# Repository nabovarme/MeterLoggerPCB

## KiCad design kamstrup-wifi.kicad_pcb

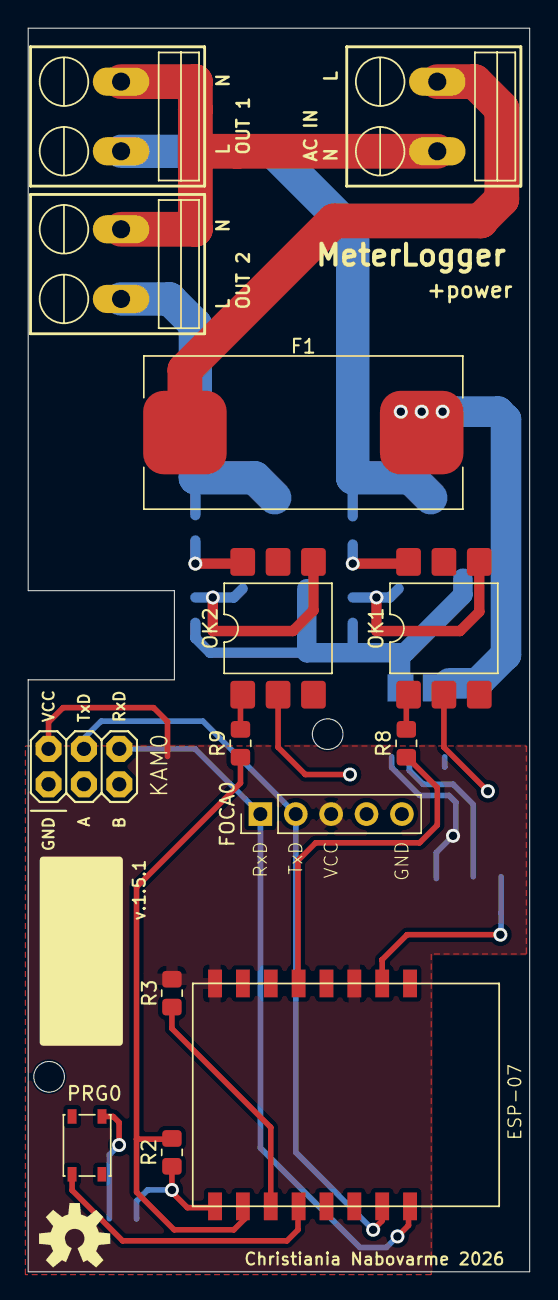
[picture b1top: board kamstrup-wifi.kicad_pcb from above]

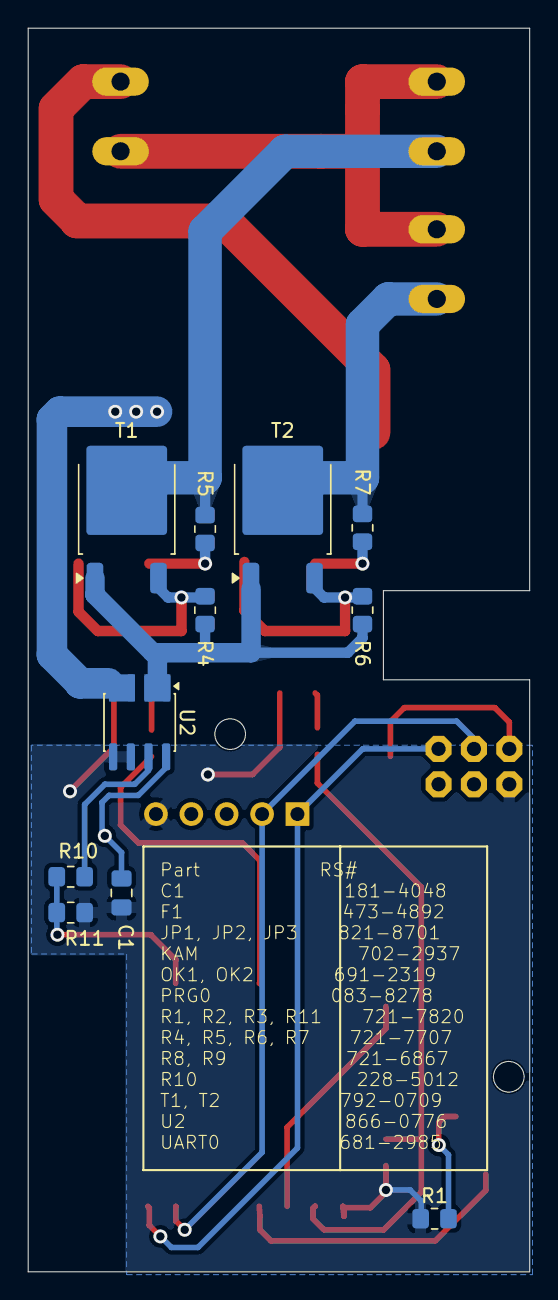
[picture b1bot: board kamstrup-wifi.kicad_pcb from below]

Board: 2 copper layers, 36.0 x 89.3 mm, 28 parts (11 on the bottom side), 23 nets.

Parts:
C1: 100nF; C_0805_2012Metric_Pad1.18x1.45mm_HandSolder
F1: Fuse; Fuseholder_Cylinder-5x20mm_Schurter_OGN-SMD_Horizontal_Open
FOCA0: M05PTH; PinHeader_1x05_P2.54mm_Vertical
JP1: AC IN; SCREWTERMINAL-5MM-2
JP2: AC OUT 1; SCREWTERMINAL-5MM-2
JP3: AC OUT 2; SCREWTERMINAL-5MM-2
KAM0: PINHD-2X3; 2X03
OK1, OK2: MOC3063S; SMDIP-6_W9.53mm
PRG0: M02PTH; SW_SPST_PTS810
R1, R2, R3, R11: 10k; R_0805_2012Metric_Pad1.20x1.40mm_HandSolder
R4, R5, R6, R7: 330; R_0805_2012Metric_Pad1.20x1.40mm_HandSolder
R8, R9: 120; R_0805_2012Metric_Pad1.20x1.40mm_HandSolder
R10: 22k; R_0805_2012Metric_Pad1.20x1.40mm_HandSolder
T1, T2: BT137; TO-252-2
U1: ESP8266-07; ESP-07
U2: ACS722LLCTR-05AB-T; SOIC-8_3.9x4.9mm_P1.27mm
U$2: OSHW-LOGO-M
UNK_HOLE_0: dummyfp0
UNK_HOLE_1: dummyfp1

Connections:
3.3V: C1.1, FOCA0.3, KAM0.2, R3.1, U1.CH_PD, U1.VCC, U2.8 (VCC)
/AC_CURRENT_SENSE: R4.2, R6.2, T1.1 (A1), T2.1 (A1), U2.1 (IP+), U2.2 (IP+)
/AC_FUSE: F1.2, U2.3 (IP-), U2.4 (IP-)
/AC_N: JP1.1, JP2.2, JP3.2
/AC_OUT_1: JP2.1, R5.2, T1.2
/AC_OUT_2: JP3.1, R7.2, T2.2
/ADC: R10.2, R11.2, U1.ADC
GND: C1.2, FOCA0.5, KAM0.1, OK1.2 (C), OK2.2 (C), R1.1, R2.1, R11.1, U1.GND, U2.5 (GND), U2.6 (BW_SEL)
unnamed: F1.1, JP1.2
unnamed: FOCA0.1, KAM0.6, U1.TXD
unnamed: FOCA0.2, KAM0.4, U1.RXD
unnamed: OK1.4 (A1), R4.1, T1.3 (G)
unnamed: OK1.6 (A2), R5.1
unnamed: OK1.1 (A), R8.2
unnamed: OK2.4 (A1), R6.1, T2.3 (G)
unnamed: OK2.6 (A2), R7.1
unnamed: OK2.1 (A), R9.2
unnamed: PRG0.1, R1.2
unnamed: PRG0.2, U1.GPIO0
unnamed: R2.2, R9.1, U1.GPIO15
unnamed: R3.2, U1.GPIO2
unnamed: R8.1, U1.GPIO14
unnamed: R10.1, U2.7 (VIOUT)

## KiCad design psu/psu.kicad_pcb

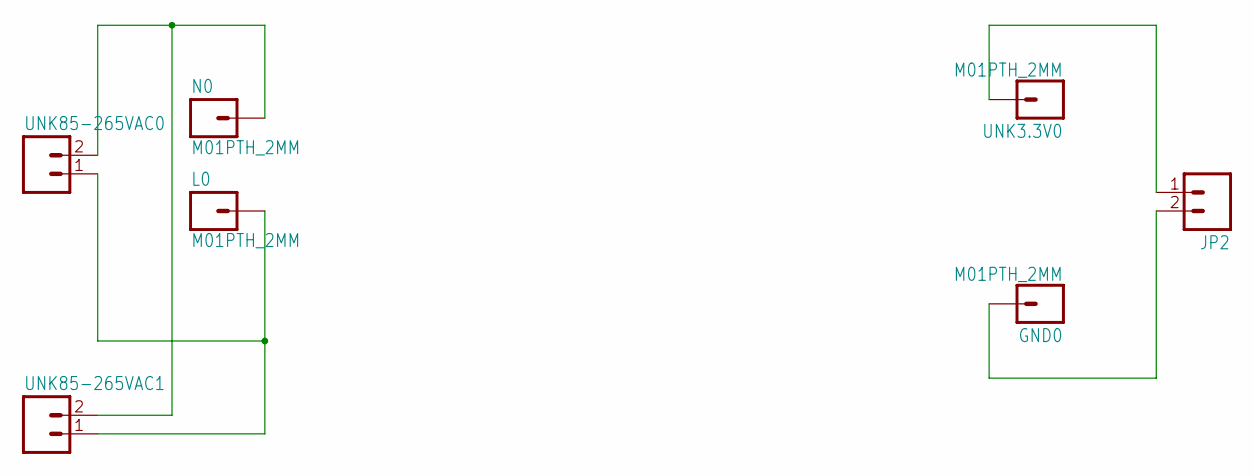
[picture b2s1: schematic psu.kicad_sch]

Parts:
GND0: M01PTH_2MM; 1X01_2MM
JP2: M02PTH3_5MM; 1X02_LONGPADS
L0: M01PTH_2MM; 1X01_2MM
N0: M01PTH_2MM; 1X01_2MM
UNK3.3V0: M01PTH_2MM; 1X01_2MM
UNK85-265VAC0, UNK85-265VAC1: M02PTH3_5MM; 1X02_LONGPADS

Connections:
unnamed: L0.1, UNK85-265VAC0.1, UNK85-265VAC1.1
unnamed: N0.1, UNK85-265VAC0.2, UNK85-265VAC1.2
unnamed: JP2.1, UNK3.3V0.1
unnamed: GND0.1, JP2.2

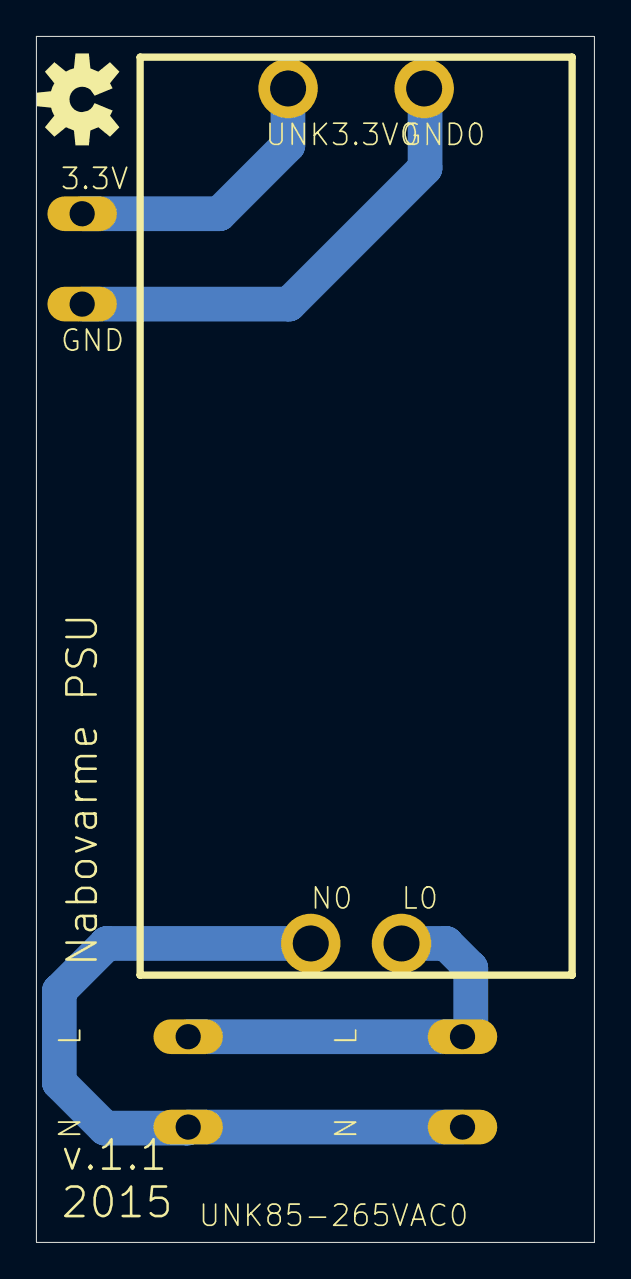
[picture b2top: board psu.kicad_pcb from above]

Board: 2 copper layers, 31.0 x 67.0 mm, 8 parts (0 on the bottom side), 4 nets.

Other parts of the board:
U$1: OSHW-LOGO-M

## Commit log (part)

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2015-09-15 added pcb+power from f81b98b96438f6aeb28dbc087c39275dec301eaf
2016-05-18 v.1.2.1
    + watchdog and pulldown on gpio 15
2016-05-29 PCB: v.1.4.1 Added FeRAM
    + docs
2016-11-19 added pull up resistor on GPIO02
2017-04-21 added missing pull down (R12) on pcb
2017-04-23 reverted pcb to v 1.2.1 2377baf1af9bc101ab4e1265beb616f56084d54c no pull down needed
2017-10-08 Labels for N and L on AC in/out
2017-10-09 pcb board made 8 mm higher for better fixation in kamstrup meter
2017-10-17 updated pdf's
    for schematics and pcb
2017-10-17 moved meterlogger_doxygen to submodule
2017-10-17 moved pcb/psu to pcb+power/psu
2017-10-19 RS # for R4, R5, R8, R9 changed
2017-10-23 Missing R11 value fixed
2017-10-23 version bumbed to 1.2.5
2017-10-25 rotated jp1, jp3 and jp3
2017-10-25 removed snubber circuits and external watchdog timer ic now version 1.3.0
2017-10-25 changed some via size v 1.3.1
2017-10-25 updated pdfs from latest version (v.1.3.1)
2018-04-27 updated psi pcb
    3.3V -> 3.6V
    v.1.1 -> v.1.2
    2015 -> 2018
2018-04-28 psu pcb: smaller holes for psu module
2018-04-28 psi pcb: better silk layout
2018-05-09 programmer connector moved
2018-05-11 Sdcard
2018-05-11 Silk updated
2018-05-11 Version sent to pcb fabrication
